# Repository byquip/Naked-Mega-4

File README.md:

# Naked Mega 4
This is hardware design of Arduino Mega 2560 core. \
This design is based on Naked Mega \
designed by [Fuzzy Studio](https://github.com/FuzzyNoodle/Fuzzy-Naked-Mega) and [geraicerdas](https://github.com/geraicerdas/Cerdas-F2).

Tutorial [here](https://www.hackster.io/news/a-bare-naked-arduino-mega-2314647cf772)

This repo is an update of `geraicerdas` design to be more like Naked Mega 4.0 \
Instead of "Batik" design in the bottom Silkscreen as an Indonesian culture from `geraicerdas`. \
I added some vyshyvanka pattern as Ukrainian culture in the bottom Silkscreen which represent my hometown name Rubizhne in "Brodivsk" writing alphabet.

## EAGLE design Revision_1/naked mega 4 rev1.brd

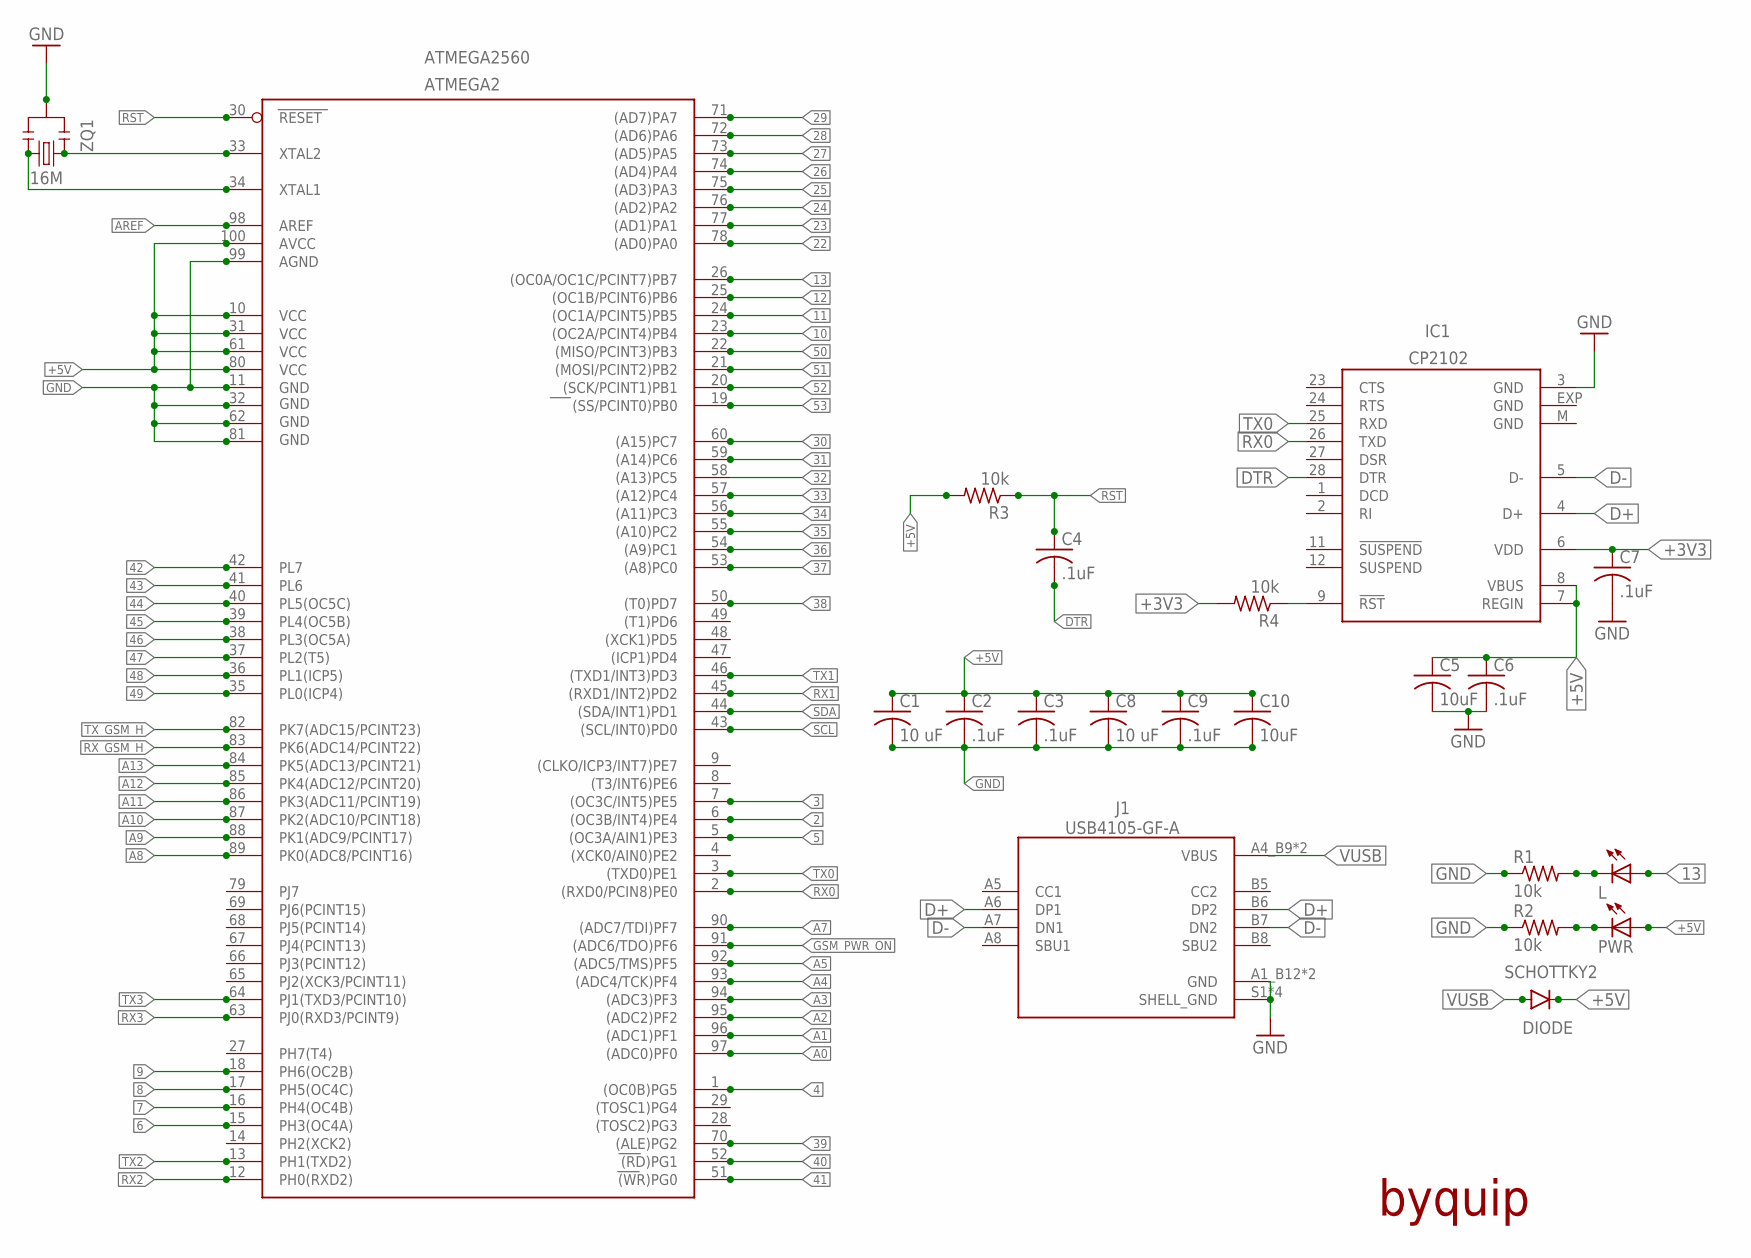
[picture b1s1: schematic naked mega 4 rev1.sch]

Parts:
ATMEGA2: ATMEGA2560; TQFP100
C1, C8: 10 uF; SMD-0805
C2, C3, C4, C6, C7, C9: .1uF; SMD-0805
C5, C10: 10uF; SMD-0805
IC1: CP2102; MLP28
J1: USB4105-GF-A; GCT_USB4105-GF-A
L: L; SMD-0805-LED
PWR: L; SMD-0805-LED
R1, R2, R3, R4: 10k; SMD-0805
SCHOTTKY2: DIODE; SOD-323
ZQ1: 16M; CSTCE*

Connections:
2: ATMEGA2.6 ((OC3B/INT4)PE4)
3: ATMEGA2.7 ((OC3C/INT5)PE5)
4: ATMEGA2.1 ((OC0B)PG5)
5: ATMEGA2.5 ((OC3A/AIN1)PE3)
6: ATMEGA2.15 (PH3(OC4A))
7: ATMEGA2.16 (PH4(OC4B))
8: ATMEGA2.17 (PH5(OC4C))
9: ATMEGA2.18 (PH6(OC2B))
10: ATMEGA2.23 ((OC2A/PCINT4)PB4)
11: ATMEGA2.24 ((OC1A/PCINT5)PB5)
12: ATMEGA2.25 ((OC1B/PCINT6)PB6)
13: ATMEGA2.26 ((OC0A/OC1C/PCINT7)PB7), L.1 (A)
22: ATMEGA2.78 ((AD0)PA0)
23: ATMEGA2.77 ((AD1)PA1)
24: ATMEGA2.76 ((AD2)PA2)
25: ATMEGA2.75 ((AD3)PA3)
26: ATMEGA2.74 ((AD4)PA4)
27: ATMEGA2.73 ((AD5)PA5)
28: ATMEGA2.72 ((AD6)PA6)
29: ATMEGA2.71 ((AD7)PA7)
30: ATMEGA2.60 ((A15)PC7)
31: ATMEGA2.59 ((A14)PC6)
32: ATMEGA2.58 ((A13)PC5)
33: ATMEGA2.57 ((A12)PC4)
34: ATMEGA2.56 ((A11)PC3)
35: ATMEGA2.55 ((A10)PC2)
36: ATMEGA2.54 ((A9)PC1)
37: ATMEGA2.53 ((A8)PC0)
38: ATMEGA2.50 ((T0)PD7)
39: ATMEGA2.70 ((ALE)PG2)
40: ATMEGA2.52 ((RD)PG1)
41: ATMEGA2.51 ((WR)PG0)
42: ATMEGA2.42 (PL7)
43: ATMEGA2.41 (PL6)
44: ATMEGA2.40 (PL5(OC5C))
45: ATMEGA2.39 (PL4(OC5B))
46: ATMEGA2.38 (PL3(OC5A))
47: ATMEGA2.37 (PL2(T5))
48: ATMEGA2.36 (PL1(ICP5))
49: ATMEGA2.35 (PL0(ICP4))
50: ATMEGA2.22 ((MISO/PCINT3)PB3)
51: ATMEGA2.21 ((MOSI/PCINT2)PB2)
52: ATMEGA2.20 ((SCK/PCINT1)PB1)
53: ATMEGA2.19 ((SS/PCINT0)PB0)
+3V3: C7.1, IC1.6 (VDD), R4.2
+5V: ATMEGA2.10 (VCC), ATMEGA2.31 (VCC1), ATMEGA2.61 (VCC2), ATMEGA2.80 (VCC3), ATMEGA2.100 (AVCC), C1.1, C2.1, C3.1, C5.1, C6.1, C8.1, C9.1, C10.1, IC1.7 (REGIN), IC1.8 (VBUS), PWR.1 (A), R3.2, SCHOTTKY2.C
A0: ATMEGA2.97 ((ADC0)PF0)
A1: ATMEGA2.96 ((ADC1)PF1)
A2: ATMEGA2.95 ((ADC2)PF2)
A3: ATMEGA2.94 ((ADC3)PF3)
A4: ATMEGA2.93 ((ADC4/TCK)PF4)
A5: ATMEGA2.92 ((ADC5/TMS)PF5)
A7: ATMEGA2.90 ((ADC7/TDI)PF7)
A8: ATMEGA2.89 (PK0(ADC8/PCINT16))
A9: ATMEGA2.88 (PK1(ADC9/PCINT17))
A10: ATMEGA2.87 (PK2(ADC10/PCINT18))
A11: ATMEGA2.86 (PK3(ADC11/PCINT19))
A12: ATMEGA2.85 (PK4(ADC12/PCINT20))
A13: ATMEGA2.84 (PK5(ADC13/PCINT21))
AREF: ATMEGA2.98 (AREF)
D+: IC1.4 (D+), J1.A6 (DP1), J1.B6 (DP2)
D-: IC1.5 (D-), J1.A7 (DN1), J1.B7 (DN2)
DTR: C4.2, IC1.28 (DTR)
GND: ATMEGA2.11 (GND), ATMEGA2.32 (GND1), ATMEGA2.62 (GND2), ATMEGA2.81 (GND3), ATMEGA2.99 (AGND), C1.2, C2.2, C3.2, C5.2, C6.2, C7.2, C8.2, C9.2, C10.2, IC1.3 (GND), IC1.EXP (GND), IC1.M (GND), J1.A1_B12 (GND), J1.B1_A12 (GND), J1.S1 (SHELL_GND), J1.S2 (SHELL_GND), J1.S3 (SHELL_GND), J1.S4 (SHELL_GND), R1.1, R2.1, ZQ1.2
GSM_PWR_ON: ATMEGA2.91 ((ADC6/TDO)PF6)
unnamed: ATMEGA2.34 (XTAL1), ZQ1.3
unnamed: ATMEGA2.33 (XTAL2), ZQ1.1
unnamed: L.2 (C), R1.2
unnamed: IC1.9 (!RST), R4.1
unnamed: PWR.2 (C), R2.2
RST: ATMEGA2.30 (RESET), C4.1, R3.1
RX0: ATMEGA2.2 ((RXD0/PCIN8)PE0), IC1.26 (TXD)
RX1: ATMEGA2.45 ((RXD1/INT2)PD2)
RX2: ATMEGA2.12 (PH0(RXD2))
RX3: ATMEGA2.63 (PJ0(RXD3/PCINT9))
RX_GSM_H: ATMEGA2.83 (PK6(ADC14/PCINT22))
SCL: ATMEGA2.43 ((SCL/INT0)PD0)
SDA: ATMEGA2.44 ((SDA/INT1)PD1)
TX0: ATMEGA2.3 ((TXD0)PE1), IC1.25 (RXD)
TX1: ATMEGA2.46 ((TXD1/INT3)PD3)
TX2: ATMEGA2.13 (PH1(TXD2))
TX3: ATMEGA2.64 (PJ1(TXD3/PCINT10))
TX_GSM_H: ATMEGA2.82 (PK7(ADC15/PCINT23))
VUSB: J1.A4_B9 (VBUS), J1.B4_A9 (VBUS), SCHOTTKY2.A

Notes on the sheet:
byquip

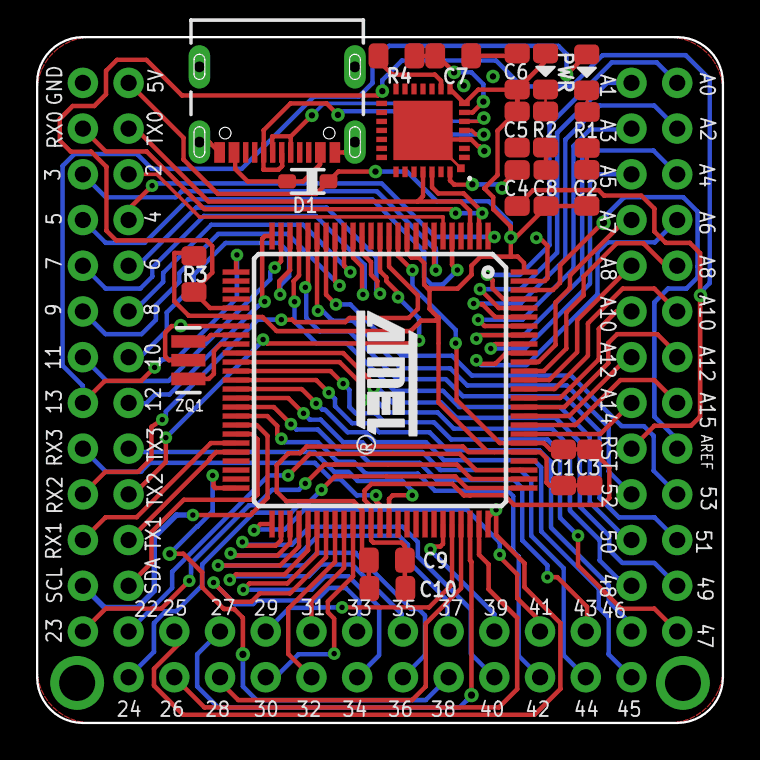
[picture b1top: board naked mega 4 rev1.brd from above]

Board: 2 copper layers, 38.1 x 38.1 mm, 22 parts (0 on the bottom side), 16 nets.

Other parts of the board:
U$4: RUBIZHNE-VYSHYVANKA-LOGO

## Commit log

2023-05-24 naked-mega-4
2023-05-24 link fix
2023-06-14 fixed wrong tx/rx connection
2023-06-14 silk lay finetuning
2023-06-14 images upd
2023-06-15 added gerber for jlcpcb
